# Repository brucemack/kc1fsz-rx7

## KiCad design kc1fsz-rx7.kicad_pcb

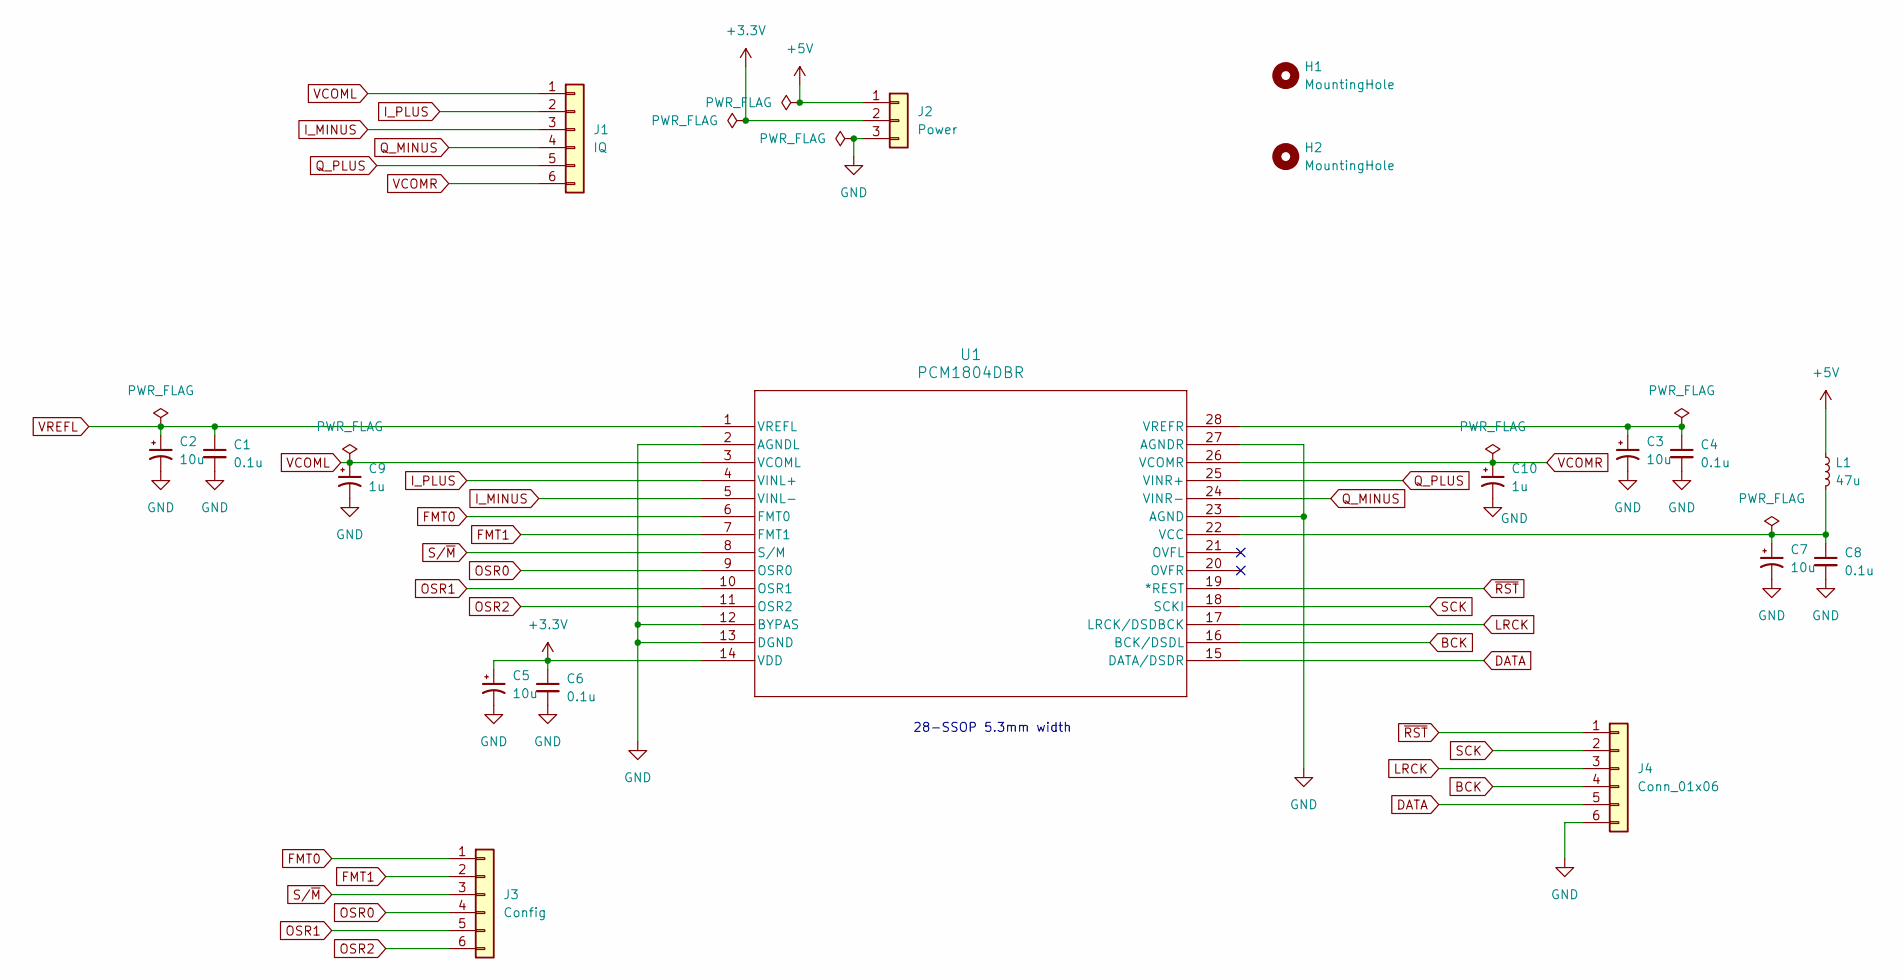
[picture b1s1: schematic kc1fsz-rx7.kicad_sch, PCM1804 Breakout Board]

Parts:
C1, C4, C6, C8: 0.1u; C_0805_2012Metric_Pad1.18x1.45mm_HandSolder
C2, C3, C5, C7: 10u; CP_Radial_D4.0mm_P2.00mm
C9, C10: 1u; C_0805_2012Metric_Pad1.18x1.45mm_HandSolder
H1, H2: MountingHole; MountingHole_3mm
J1: IQ; PinHeader_1x06_P2.54mm_Vertical
J2: Power; PinHeader_1x03_P2.54mm_Vertical
J3: Config; PinHeader_1x06_P2.54mm_Vertical
J4: Conn_01x06; PinHeader_1x06_P2.54mm_Vertical
L1: 47u; L_0805_2012Metric_Pad1.15x1.40mm_HandSolder
U1: PCM1804DBR; SSOP-28_5.3x10.2mm_P0.65mm

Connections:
+3.3V: C5.1, C6.1, J2.2, U1.14 (VDD)
+5V: J2.1, L1.1
BCK: J4.4, U1.16 (BCK/DSDL)
DATA: J4.5, U1.15 (DATA/DSDR)
FMT0: J3.1, U1.6 (FMT0)
FMT1: J3.2, U1.7 (FMT1)
GND: C1.2, C2.2, C3.2, C4.2, C5.2, C6.2, C7.2, C8.2, C9.2, C10.2, J2.3, J4.6, U1.2 (AGNDL), U1.12 (BYPAS), U1.13 (DGND), U1.23 (AGND), U1.27 (AGNDR)
I_MINUS: J1.3, U1.5 (VINL-)
I_PLUS: J1.2, U1.4 (VINL+)
LRCK: J4.3, U1.17 (LRCK/DSDBCK)
unnamed: C7.1, C8.1, L1.2, U1.22 (VCC)
unnamed: C3.1, C4.1, U1.28 (VREFR)
OSR0: J3.4, U1.9 (OSR0)
OSR1: J3.5, U1.10 (OSR1)
OSR2: J3.6, U1.11 (OSR2)
Q_MINUS: J1.4, U1.24 (VINR-)
Q_PLUS: J1.5, U1.25 (VINR+)
SCK: J4.2, U1.18 (SCKI)
S/~M: J3.3, U1.8 (S/M)
VCOML: C9.1, J1.1, U1.3 (VCOML)
VCOMR: C10.1, J1.6, U1.26 (VCOMR)
VREFL: C1.1, C2.1, U1.1 (VREFL)
~RST: J4.1, U1.19 (*REST)

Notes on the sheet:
28-SSOP 5.3mm width

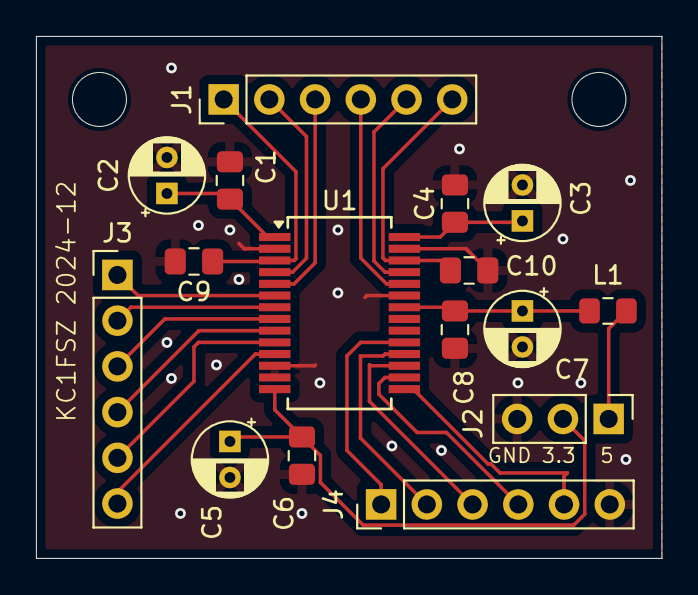
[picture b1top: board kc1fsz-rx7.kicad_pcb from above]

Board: 2 copper layers, 34.8 x 29.0 mm, 18 parts (0 on the bottom side), 23 nets.

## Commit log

2024-12-03 Added docs
2024-12-03 Final board being sent to OSHPARK
2025-01-15 Working
